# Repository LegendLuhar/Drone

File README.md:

# ELEC 327 Drone Final Project

This repository contains all necessary files for the ELEC 327 Final Project (Custom Drone)

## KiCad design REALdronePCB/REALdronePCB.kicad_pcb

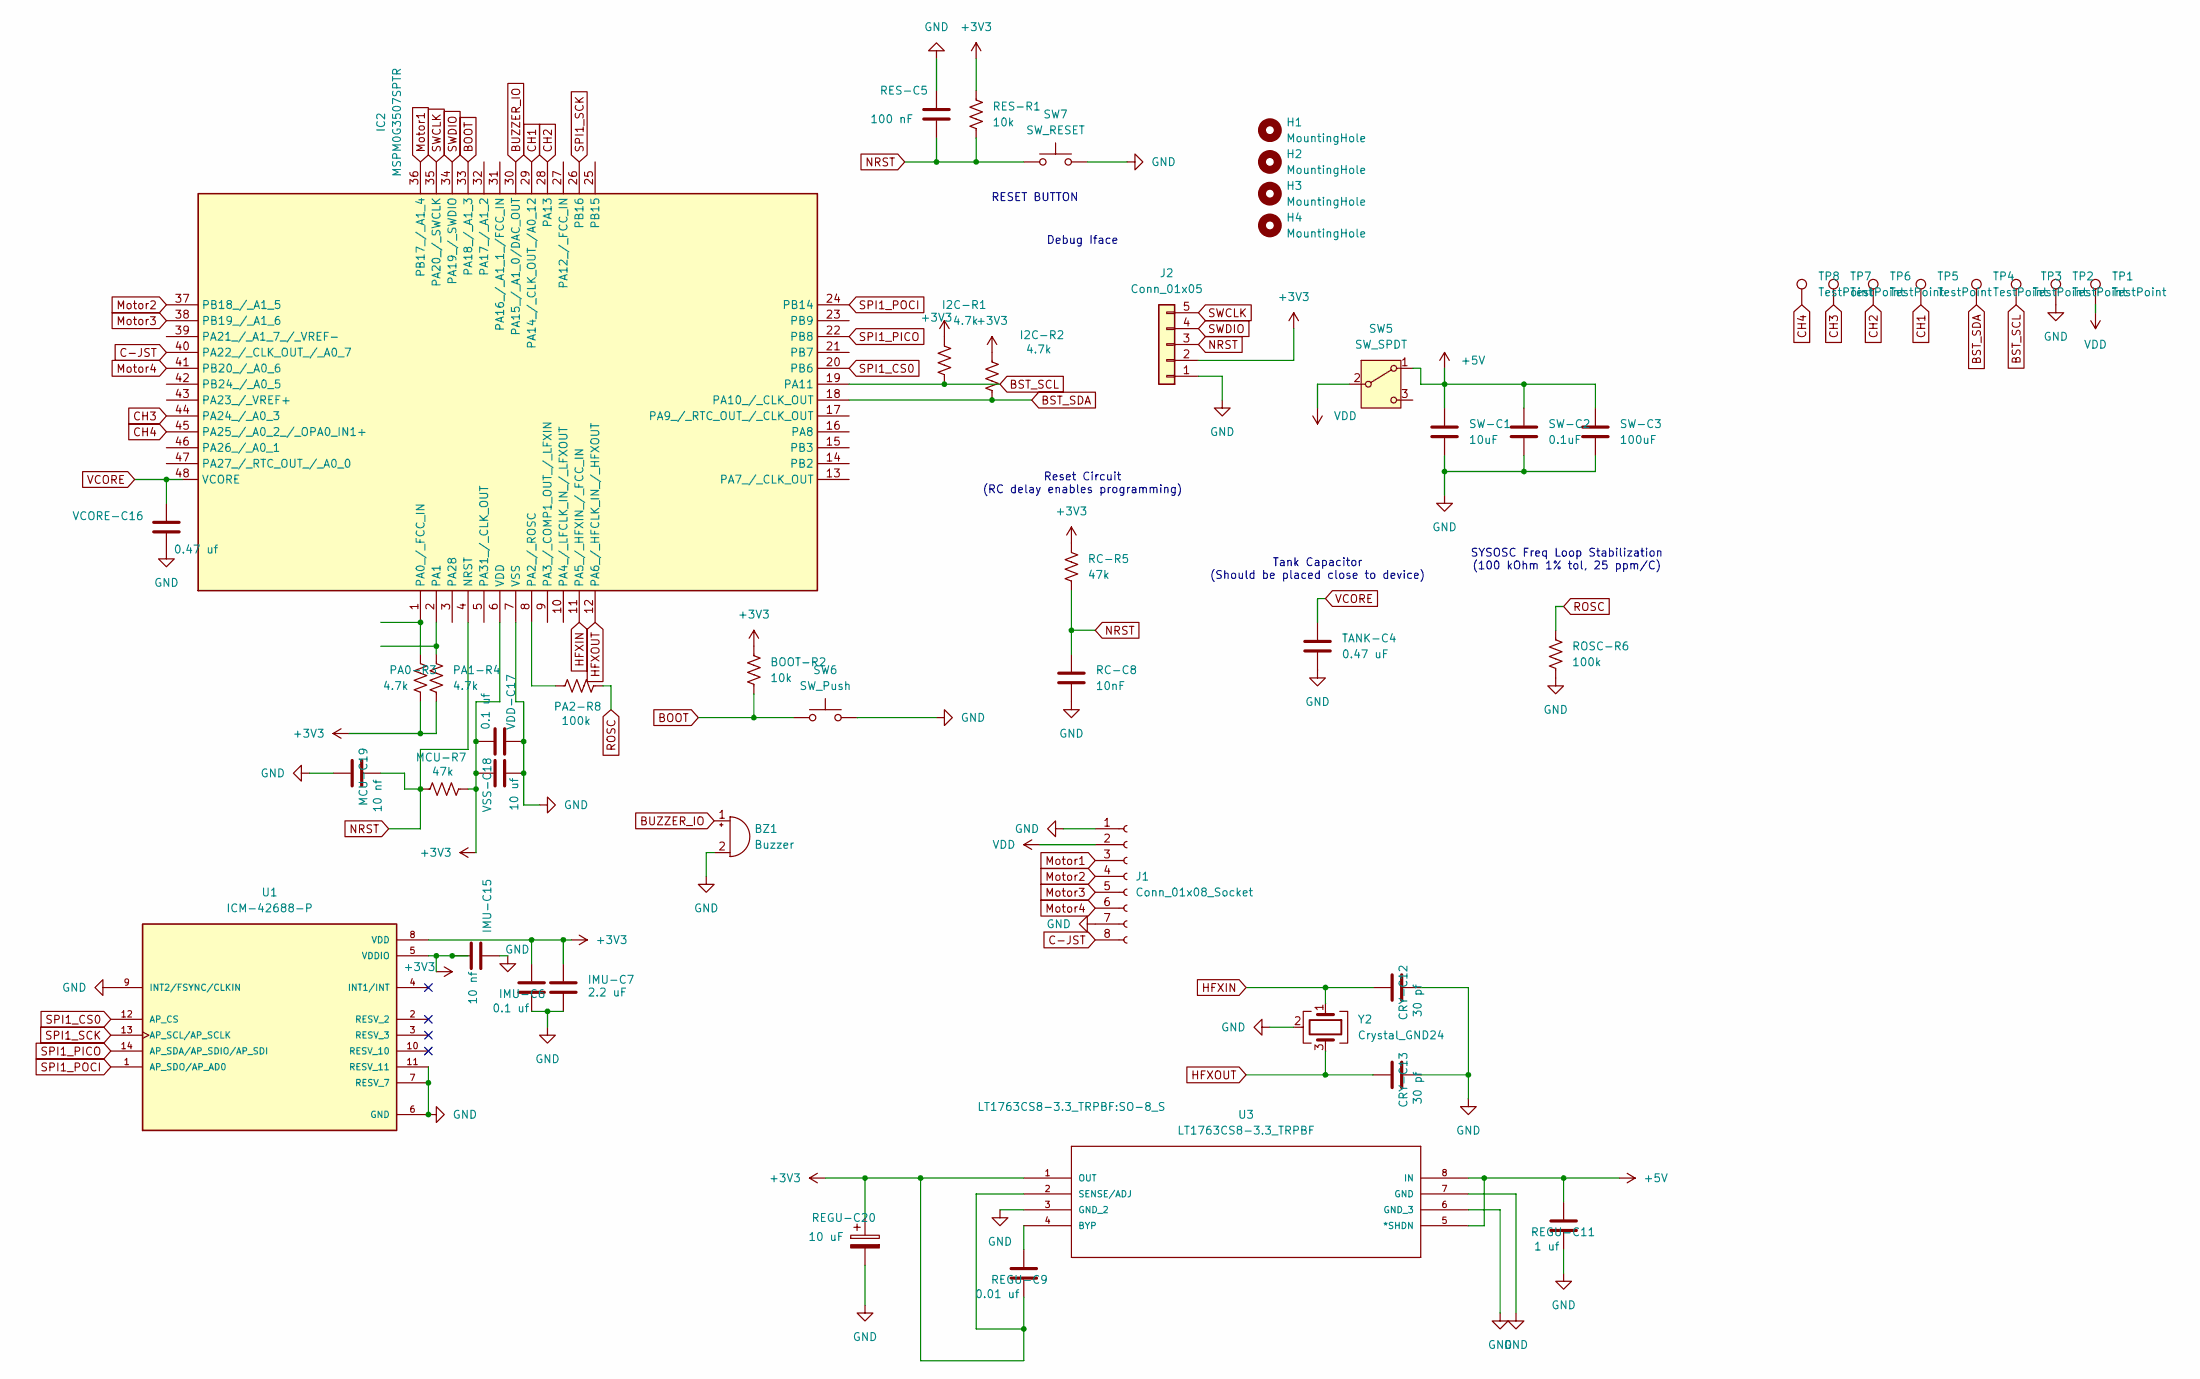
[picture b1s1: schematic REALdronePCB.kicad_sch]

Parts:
BOOT-R2: 10k; R_0805_2012Metric_Pad1.20x1.40mm_HandSolder
BZ1: Buzzer; Buzzer_Murata_PKLCS1212E; LCSC Part # C113159
CRY-C12, CRY-C13: 30 pf; C_1206_3216Metric_Pad1.33x1.80mm_HandSolder
H1, H2, H3, H4: MountingHole; DroneTHTPad
I2C-R1, I2C-R2: 4.7k; R_0805_2012Metric_Pad1.20x1.40mm_HandSolder; LCSC Part # C105579
IC2: MSPM0G3507SPTR; QFP50P900X900X160-48N; Mouser Part Number 595-MSPM0G3507SPTR
IMU-C6: 0.1 uf; C_1206_3216Metric_Pad1.33x1.80mm_HandSolder
IMU-C7: 2.2 uF; C_1206_3216Metric_Pad1.33x1.80mm_HandSolder
IMU-C15: 10 nf; C_1206_3216Metric_Pad1.33x1.80mm_HandSolder
J1: Conn_01x08_Socket; JST_SH_SM08B-SRSS-TB_1x08-1MP_P1.00mm_Horizontal
J2: Conn_01x05; PinHeader_1x05_P2.54mm_Horizontal; LCSC Part # C492413
MCU-C19: 10 nf; C_1206_3216Metric_Pad1.33x1.80mm_HandSolder
MCU-R7: 47k; R_0805_2012Metric_Pad1.20x1.40mm_HandSolder
PA0-R3, PA1-R4: 4.7k; R_0805_2012Metric_Pad1.20x1.40mm_HandSolder
PA2-R8: 100k; R_0805_2012Metric_Pad1.20x1.40mm_HandSolder
RC-C8: 10nF; C_1206_3216Metric_Pad1.33x1.80mm_HandSolder; LCSC Part # C15195
RC-R5: 47k; R_0805_2012Metric_Pad1.20x1.40mm_HandSolder; LCSC Part # C105579
REGU-C9: 0.01 uf; C_1206_3216Metric_Pad1.33x1.80mm_HandSolder
REGU-C11: 1 uf; C_1206_3216Metric_Pad1.33x1.80mm_HandSolder
REGU-C20: 10 uF; C_0805_2012Metric_Pad1.18x1.45mm_HandSolder
RES-C5: 100 nF; C_1206_3216Metric_Pad1.33x1.80mm_HandSolder
RES-R1: 10k; R_0805_2012Metric_Pad1.20x1.40mm_HandSolder
ROSC-R6: 100k; R_0805_2012Metric_Pad1.20x1.40mm_HandSolder; LCSC Part # C60491
SW5: SW_SPDT; SW_EG1270; MPN C20611678; LCSC Part # C20611678
SW6: SW_Push; SW_SPST_B3U-1000P
SW7: SW_RESET; SW_SPST_B3U-1000P
SW-C1: 10uF; C_0603_1608Metric; LCSC Part # C19702
SW-C2: 0.1uF; C_0603_1608Metric_Pad1.08x0.95mm_HandSolder; LCSC Part # C1591
SW-C3: 100uF; C_1206_3216Metric; LCSC Part # C15008
TANK-C4: 0.47 uF; C_1206_3216Metric_Pad1.33x1.80mm_HandSolder; LCSC Part # C13967
TP1, TP2, TP3, TP4, TP5, TP6, TP7, TP8: TestPoint; TestPoint_Pad_1.0x1.0mm
U1: ICM-42688-P; LGA-14_3x2.5mm_P0.5mm_LayoutBorder3x4y; PARTREV 1.2
U3: LT1763CS8-3.3_TRPBF; SO-8_S; MANUFACTURER_PART_NUMBER lt1763cs8
VCORE-C16: 0.47 uf; C_1206_3216Metric_Pad1.33x1.80mm_HandSolder
VDD-C17: 0.1 uf; C_1206_3216Metric_Pad1.33x1.80mm_HandSolder
VSS-C18: 10 uf; C_1206_3216Metric_Pad1.33x1.80mm_HandSolder
Y2: Crystal_GND24; Crystal_SMD_5032-4Pin_5.0x3.2mm

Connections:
+3V3: BOOT-R2.1, I2C-R1.2, I2C-R2.2, IC2.6 (VDD), IMU-C6.1, IMU-C7.1, IMU-C15.1, J2.2, MCU-R7.2, PA0-R3.2, PA1-R4.2, RC-R5.2, REGU-C9.2, REGU-C20.1, RES-R1.1, U1.5 (VDDIO), U1.8 (VDD), U3.1 (OUT), U3.2 (SENSE/ADJ), VDD-C17.1, VSS-C18.1
+5V: REGU-C11.1, SW5.1 (A), SW-C1.1, SW-C2.1, SW-C3.1, U3.5 (*SHDN), U3.8 (IN)
BOOT: BOOT-R2.2, IC2.33 (PA18_/_A1_3), SW6.1
BST_SCL: I2C-R1.1, IC2.19 (PA11), TP3.1 (1_1)
BST_SDA: I2C-R2.1, IC2.18 (PA10_/_CLK_OUT), TP4.1 (1_1)
BUZZER_IO: BZ1.1 (+), IC2.30 (PA15_/_A1_0/DAC_OUT)
C-JST: IC2.40 (PA22_/_CLK_OUT_/_A0_7), J1.8
CH1: IC2.29 (PA14_/_CLK_OUT_/A0_12), TP5.1 (1_1)
CH2: IC2.28 (PA13), TP6.1 (1_1)
CH3: IC2.44 (PA24_/_A0_3), TP7.1 (1_1)
CH4: IC2.45 (PA25_/_A0_2_/_OPA0_IN1+), TP8.1 (1_1)
GND: BZ1.2 (-), CRY-C12.2, CRY-C13.2, IC2.7 (VSS), IMU-C6.2, IMU-C7.2, IMU-C15.2, J1.1, J1.7, J2.1, MCU-C19.1, RC-C8.2, REGU-C11.2, REGU-C20.2, RES-C5.1, ROSC-R6.1, SW6.2, SW7.2, SW-C1.2, SW-C2.2, SW-C3.2, TANK-C4.2, TP2.1 (1_1), U1.6 (GND), U1.7 (RESV_7), U1.9 (INT2/FSYNC/CLKIN), U1.11 (RESV_11), U3.3 (GND_2), U3.6 (GND_3), U3.7 (GND), VCORE-C16.1, VDD-C17.2, VSS-C18.2, Y2.2 (G), Y2.4 (G)
HFXIN: CRY-C12.1, IC2.11 (PA5_/_HFXIN_/_FCC_IN), Y2.1
HFXOUT: CRY-C13.1, IC2.12 (PA6_/_HFCLK_IN_/_HFXOUT), Y2.3
Motor1: IC2.36 (PB17_/_A1_4), J1.3
Motor2: IC2.37 (PB18_/_A1_5), J1.4
Motor3: IC2.38 (PB19_/_A1_6), J1.5
Motor4: IC2.41 (PB20_/_A0_6), J1.6
NRST: IC2.4 (NRST), J2.3, MCU-C19.2, MCU-R7.1, RC-C8.1, RC-R5.1, RES-C5.2, RES-R1.2, SW7.1
unnamed: IC2.1 (PA0_/_FCC_IN), PA0-R3.1
unnamed: IC2.2 (PA1), PA1-R4.1
unnamed: IC2.8 (PA2_/_ROSC), PA2-R8.1
unnamed: REGU-C9.1, U3.4 (BYP)
ROSC: PA2-R8.2, ROSC-R6.2
SPI1_CS0: IC2.20 (PB6), U1.12 (AP_CS)
SPI1_PICO: IC2.22 (PB8), U1.14 (AP_SDA/AP_SDIO/AP_SDI)
SPI1_POCI: IC2.24 (PB14), U1.1 (AP_SDO/AP_AD0)
SPI1_SCK: IC2.26 (PB16), U1.13 (AP_SCL/AP_SCLK)
SWCLK: IC2.35 (PA20_/_SWCLK), J2.5
SWDIO: IC2.34 (PA19_/_SWDIO), J2.4
VCORE: IC2.48 (VCORE), TANK-C4.1, VCORE-C16.2
VDD: J1.2, SW5.2 (B), TP1.1 (1_1)

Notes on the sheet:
RESET BUTTON
SYSOSC Freq Loop Stabilization (100 kOhm 1% tol, 25 ppm/C)
Reset Circuit (RC delay enables programming)
Debug Iface
Tank Capacitor (Should be placed close to device)

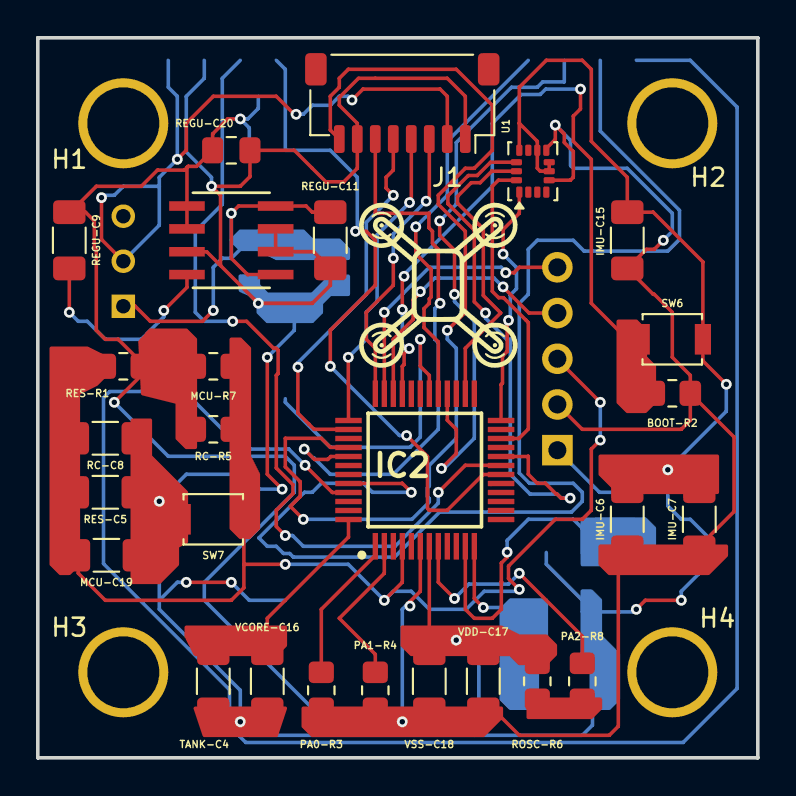
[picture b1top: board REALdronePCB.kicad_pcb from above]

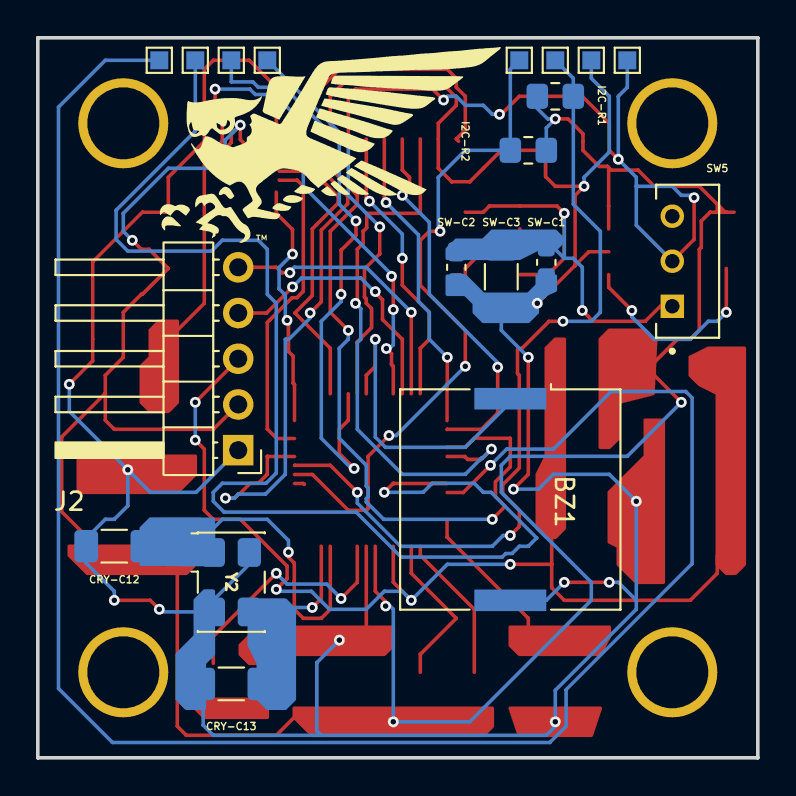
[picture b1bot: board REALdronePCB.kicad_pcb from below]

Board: 2 copper layers, 40.0 x 40.0 mm, 50 parts (19 on the bottom side), 32 nets.

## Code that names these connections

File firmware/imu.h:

/*
 * imu.h — ICM-42688-P 6-axis IMU driver, SPI1, polled.
 *
 * Pin / mux assignment (project_drone_hardware.md):
 *   PB6  PINCM23  SPI1_CS0   (PF=3)  — driven as GPIO output, manual CS
 *   PB8  PINCM25  SPI1_PICO  (PF=3)
 *   PB14 PINCM31  SPI1_POCI  (PF=3)
 *   PB16 PINCM33  SPI1_SCLK  (PF=3)
 *
 * SPI1 isn't used by the DShot path (which lives on TIMA0/TIMA1/TIMG8 + DMA),
 * and the IMU pins (PB6/8/14/16) are disjoint from the motor pins
 * (PB17..PB20), so this driver coexists with the DShot stack on the same
 * GPIOB block — provided the GPIOB power-up is idempotent (it is).
 *
 * INT1 is no-connect and INT2 is tied to GND on this board, so there is no
 * data-ready IRQ available. Samples are polled from the scheduler tick.
 *
 * Bring-up milestone: imu_who_am_i_seen == 0x47 over SWD.
 */

#ifndef IMU_H
#define IMU_H

#include <stdint.h>
#include <stdbool.h>

typedef struct {
    int16_t accel_x;
    int16_t accel_y;
    int16_t accel_z;
    int16_t gyro_x;
    int16_t gyro_y;
    int16_t gyro_z;
    int16_t temp;
} imu_sample_t;

/* Configure SPI1 + CS pin, soft-reset the chip, verify WHO_AM_I, enable
 * gyro+accel in low-noise mode, set ODRs. Safe to call after dshot_init() and
 * after __enable_irq() — internal blocking delays are spinloops in thread
 * context and don't block the DShot ISR. Sets imu_ready on success. */
void imu_init(void);

/* Read the 14-byte temp+accel+gyro burst into *out. Returns false if the IMU
 * never initialized, or *out is NULL, or the SPI transfer aborted early.
 * ~30 µs at 4 MHz SPI bit clock, runs in thread context. */
bool imu_read_sample(imu_sample_t *out);

/* Diagnostic counters and last-seen state. All volatile so a SWD watch
 * window can see them updating live. */
extern volatile bool      imu_ready;            /* WHO_AM_I + config OK */
extern volatile uint8_t   imu_who_am_i_seen;    /* last raw WHO_AM_I byte */
extern volatile uint8_t   imu_init_status;      /* see imu_init_status_t */
extern volatile uint32_t  imu_sample_count;     /* successful reads */
extern volatile uint32_t  imu_read_failures;    /* failed reads */
extern volatile imu_sample_t imu_latest_sample; /* most recent good sample */

typedef enum {
    IMU_STATUS_BOOT             = 0,
    IMU_STATUS_WHOAMI_FAIL      = 1,
    IMU_STATUS_CONFIG_WRITE_FAIL= 2,
    IMU_STATUS_OK               = 3,
} imu_init_status_t;

#endif /* IMU_H */

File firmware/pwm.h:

/*
 * pwm.h — 50 Hz servo PWM driver for 4 motors.
 *
 * Same pin assignment as dshot.h:
 *   Motor1  PB17  PINCM43  TIMA1_CCP0 (PF=5)
 *   Motor2  PB18  PINCM44  TIMA1_CCP1 (PF=5)
 *   Motor3  PB19  PINCM45  TIMG8_CCP1 (PF=4)
 *   Motor4  PB20  PINCM48  TIMA0_CCP1 (PF=7)
 *
 * Each timer is in standalone edge-aligned PWM mode — no DMA, no event
 * fabric, no inter-timer synchronization. To change a motor's pulse width
 * you just write the timer's CC register; the change takes effect on the
 * next period boundary.
 *
 * Output: 50 Hz period (20 ms) with 1000-2000 µs pulse width. The pin is
 * HIGH for the pulse duration at the start of each 20 ms period, then LOW.
 * This is the standard servo PWM that every BLHeli / AM32 ESC auto-detects
 * on power-up.
 *
 * Arming procedure: drive 1000 µs (PWM_PULSE_MIN_US) for ~2 seconds after
 * ESC power-up. The ESC plays its arm tone, then accepts 1000-2000 µs
 * throttle values.
 */

#ifndef PWM_H
#define PWM_H

#include <stdint.h>

#define PWM_NUM_MOTORS  (4u)

typedef enum {
    PWM_MOTOR_1 = 0,
    PWM_MOTOR_2 = 1,
    PWM_MOTOR_3 = 2,
    PWM_MOTOR_4 = 3,
} pwm_motor_t;

/* Standard servo PWM pulse widths in microseconds. */
#define PWM_PULSE_MIN_US  (1000u)   /* idle / armed-min throttle */
#define PWM_PULSE_MAX_US  (2000u)   /* full throttle */

/* Configure GPIO, all three timers (TIMA1, TIMG8, TIMA0), and start them
 * counting. All four motors come up at PWM_PULSE_MIN_US (idle). Call once
 * during boot, before __enable_irq(). */
void pwm_init(void);

/* Update one motor's pulse width. Clamped to [PWM_PULSE_MIN_US,
 * PWM_PULSE_MAX_US]. Takes effect on the next 20 ms period boundary.
 * Safe to call from an ISR. */
void pwm_set_value(pwm_motor_t m, uint16_t pulse_us);

/* Convenience: drive all four motors to PWM_PULSE_MIN_US (1000 µs). Use
 * during the arm-hold window. */
void pwm_set_all_min(void);

#endif /* PWM_H */

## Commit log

2026-04-25 PCB Added
    Should be the final rendition of the PCB
2026-04-25 MISC
    other files going through now
2026-04-27 FixedPCB
    This is the final version.
2026-04-27 Add README for Simon Accelerometer project
2026-04-27 Simon Accelerometer Project
2026-04-27 Reorganized files
2026-04-27 Add initial README for Simon Accelerometer project
2026-04-27 Rename project and update description
2026-04-28 Fix typo in README description
2026-04-28 Add project description to README.md
2026-05-06 Rename README.md to Simon_README.md
2026-05-14 internmediary
2026-05-15 dshot motor actuation
2026-05-16 DShot improved, PWM tried but failed
2026-05-16 Create README.md for drone firmware documentation
    Add detailed README for drone firmware project, including hardware specs, file layout, DShot driver details, and build instructions.
2026-05-16 Final dshot_test.c
2026-05-16 Final Code Submission
